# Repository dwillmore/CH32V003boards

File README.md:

# CH32V003 dev boards meant for breadboard use.  
They have a all of the chip connections brough out to a SIP header on one side of the board which can be plugged into the outer row of pins on a breadboard--leaving all of the rest of the board available for other components and routing.

All boards have USB-C connections for data and/or power.  The data is connected via two series resistors.  Not populating these allows the pins on the chip to be used for something else.

The on board 3.3V regulator can be left off and bypassed to run the board on Vbus power.  The regulator is used for when the D+/D- lines are connected to use use from the CH32V003 via rv003usb.  

The three pin header is for plugging in a debugger like the funprog or WCH Link-E.  It exposes Vcc, SWD, and GND.

New for V4:
- Change to the popular 1117 style regulator.
- Increase size of decoupling caps to 1206
- Move as many components to the front as possible (not an option on 8 pin) to improve manufacturability
- Add 16 pin variant by popular demand

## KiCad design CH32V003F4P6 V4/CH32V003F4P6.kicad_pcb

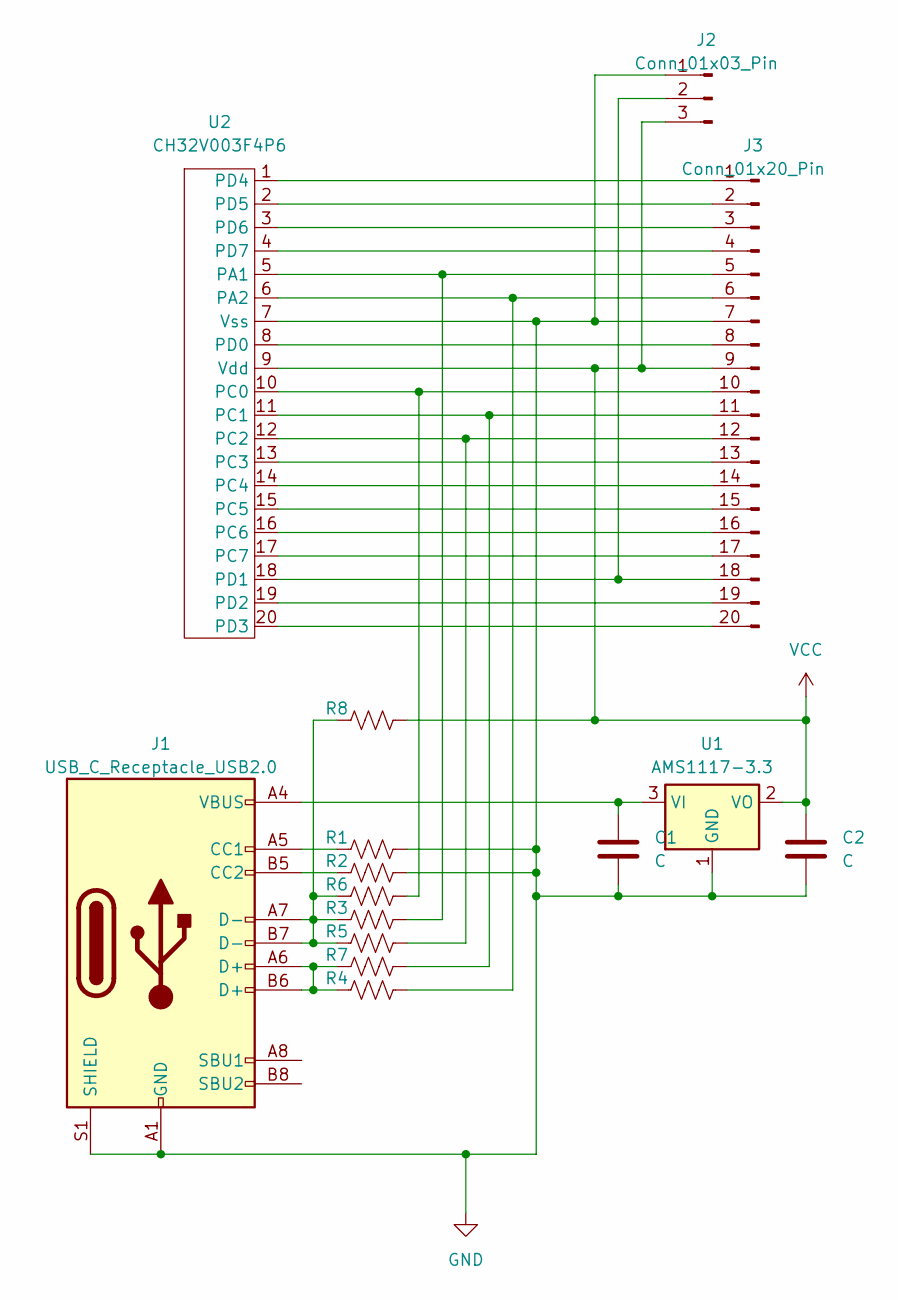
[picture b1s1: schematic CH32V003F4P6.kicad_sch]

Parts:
C1, C2: C; C_1206_3216Metric_Pad1.33x1.80mm_HandSolder
J1: USB_C_Receptacle_USB2.0; USB_C_Receptacle_HRO_TYPE-C-31-M-12
J2: Conn_01x03_Pin; PinHeader_1x03_P2.54mm_Vertical
J3: Conn_01x20_Pin; PinHeader_1x20_P2.54mm_Vertical
R1, R2, R3, R4, R5, R6, R7, R8: R_US; R_0603_1608Metric
U1: AMS1117-3.3; SOT-223-3_TabPin2
U2: CH32V003F4P6; TSSOP-20_4.4x6.5mm_P0.65mm

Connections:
GND: C1.2, C2.2, J1.A1 (GND), J1.A12 (GND), J1.B1 (GND), J1.B12 (GND), J1.S1 (SHIELD), J2.1, J3.7, R1.2, R2.2, U1.1 (GND), U2.7 (Vss)
unnamed: J1.A5 (CC1), R1.1
unnamed: J1.B5 (CC2), R2.1
unnamed: J1.A6 (D+), J1.B6 (D+), R4.1, R7.1
unnamed: J1.A7 (D-), J1.B7 (D-), R3.1, R5.1, R6.1, R8.1
unnamed: J2.2, J3.18, U2.18 (PD1)
unnamed: J3.1, U2.1 (PD4)
unnamed: J3.2, U2.2 (PD5)
unnamed: J3.3, U2.3 (PD6)
unnamed: J3.4, U2.4 (PD7)
unnamed: J3.5, R3.2, U2.5 (PA1)
unnamed: J3.6, R4.2, U2.6 (PA2)
unnamed: J3.8, U2.8 (PD0)
unnamed: J3.10, R6.2, U2.10 (PC0)
unnamed: J3.11, R7.2, U2.11 (PC1)
unnamed: J3.12, R5.2, U2.12 (PC2)
unnamed: J3.13, U2.13 (PC3)
unnamed: J3.14, U2.14 (PC4)
unnamed: J3.15, U2.15 (PC5)
unnamed: J3.16, U2.16 (PC6)
unnamed: J3.17, U2.17 (PC7)
unnamed: J3.19, U2.19 (PD2)
unnamed: J3.20, U2.20 (PD3)
unnamed: C1.1, J1.A4 (VBUS), J1.A9 (VBUS), J1.B4 (VBUS), J1.B9 (VBUS), U1.3 (VI)
VCC: C2.1, J2.3, J3.9, R8.2, U1.2 (VO), U2.9 (Vdd)

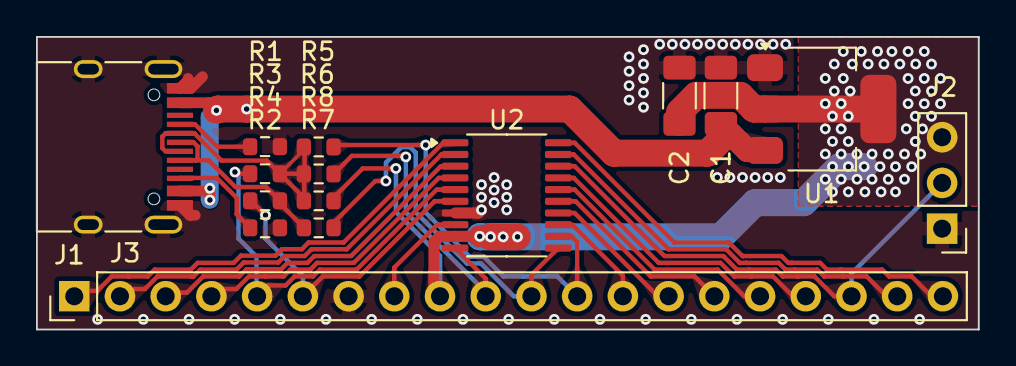
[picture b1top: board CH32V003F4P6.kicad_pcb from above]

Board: 2 copper layers, 52.3 x 16.3 mm, 15 parts (0 on the bottom side), 25 nets.

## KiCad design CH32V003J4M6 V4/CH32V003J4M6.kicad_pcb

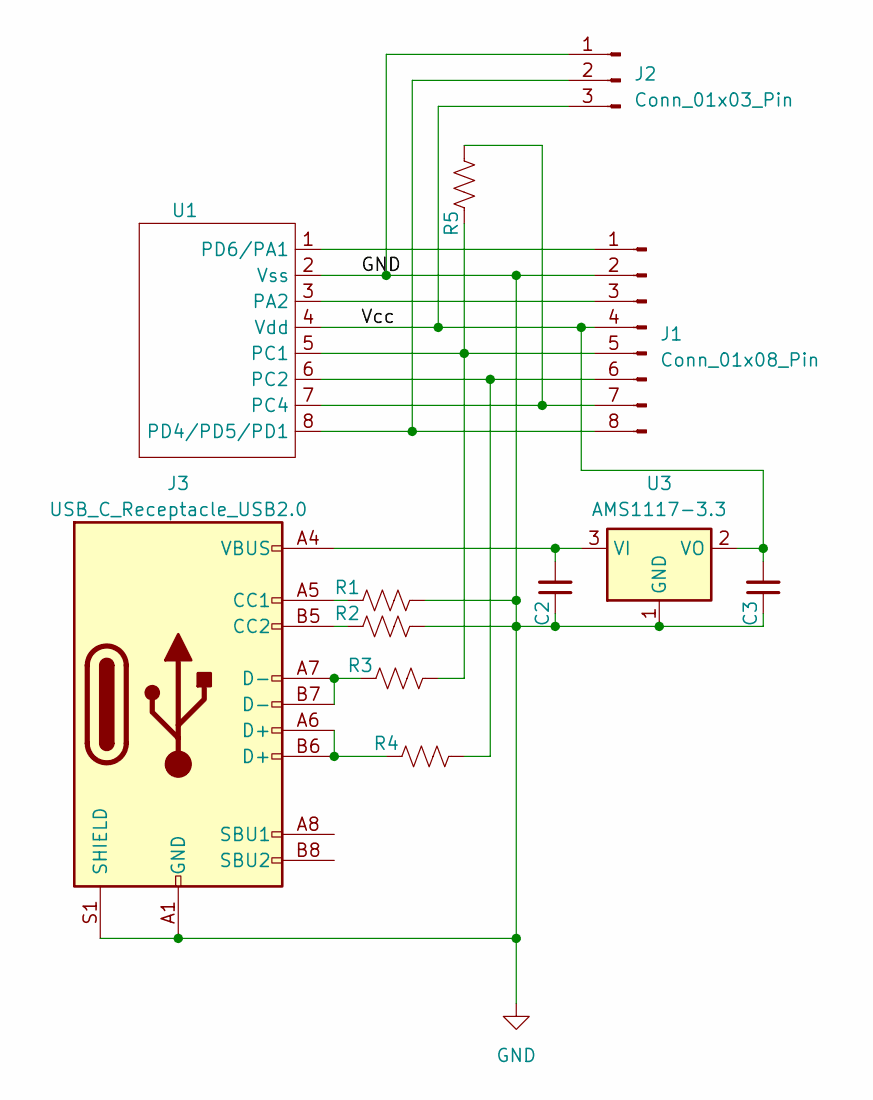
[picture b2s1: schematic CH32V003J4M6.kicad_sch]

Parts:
C2, C3: C_Small; C_0603_1608Metric
J1: Conn_01x08_Pin; PinHeader_1x08_P2.54mm_Vertical
J2: Conn_01x03_Pin; PinHeader_1x03_P2.54mm_Vertical
J3: USB_C_Receptacle_USB2.0; USB_C_Receptacle_HRO_TYPE-C-31-M-12
R1, R2, R3, R4, R5: R_US; R_0603_1608Metric
U1: SO-8_3.9x4.9mm_P1.27mm
U3: AMS1117-3.3; SOT-223-3_TabPin2

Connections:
/Vcc: C3.2, J1.4, J2.3, U1.4 (Vdd), U3.2 (VO)
GND: C2.1, C3.1, J1.2, J2.1, J3.A1 (GND), J3.A12 (GND), J3.B1 (GND), J3.B12 (GND), J3.S1 (SHIELD), R1.2, R2.2, U1.2 (Vss), U3.1 (GND)
unnamed: J1.1, U1.1 (PD6/PA1)
unnamed: J1.3, U1.3 (PA2)
unnamed: J1.5, R3.2, R5.1, U1.5 (PC1)
unnamed: J1.6, R4.2, U1.6 (PC2)
unnamed: J1.7, R5.2, U1.7 (PC4)
unnamed: J1.8, J2.2, U1.8 (PD4/PD5/PD1)
unnamed: J3.A5 (CC1), R1.1
unnamed: J3.B5 (CC2), R2.1
unnamed: J3.A6 (D+), J3.B6 (D+), R4.1
unnamed: J3.A7 (D-), J3.B7 (D-), R3.1
unnamed: C2.2, J3.A4 (VBUS), J3.A9 (VBUS), J3.B4 (VBUS), J3.B9 (VBUS), U3.3 (VI)

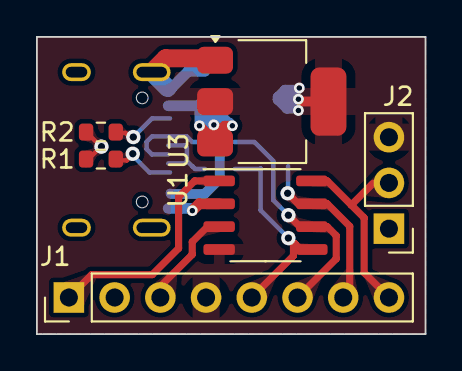
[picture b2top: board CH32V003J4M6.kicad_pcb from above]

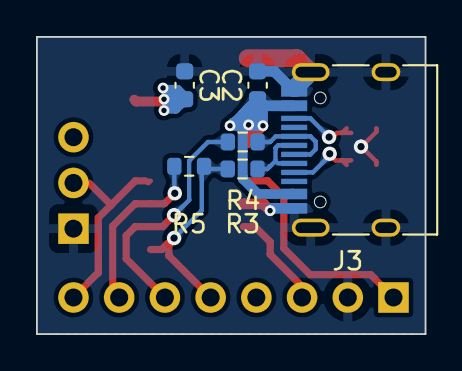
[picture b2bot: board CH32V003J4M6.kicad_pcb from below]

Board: 2 copper layers, 21.6 x 16.5 mm, 12 parts (6 on the bottom side), 13 nets.

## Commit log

2025-02-15 First upload
    This is my V3 of my single sided CH32V003 boards meant for breadboard use.
2025-08-03 Add V4 board
2025-08-03 Update README.md
    Changes for V4
2025-08-03 Update README.md
    Add V4 board pics
